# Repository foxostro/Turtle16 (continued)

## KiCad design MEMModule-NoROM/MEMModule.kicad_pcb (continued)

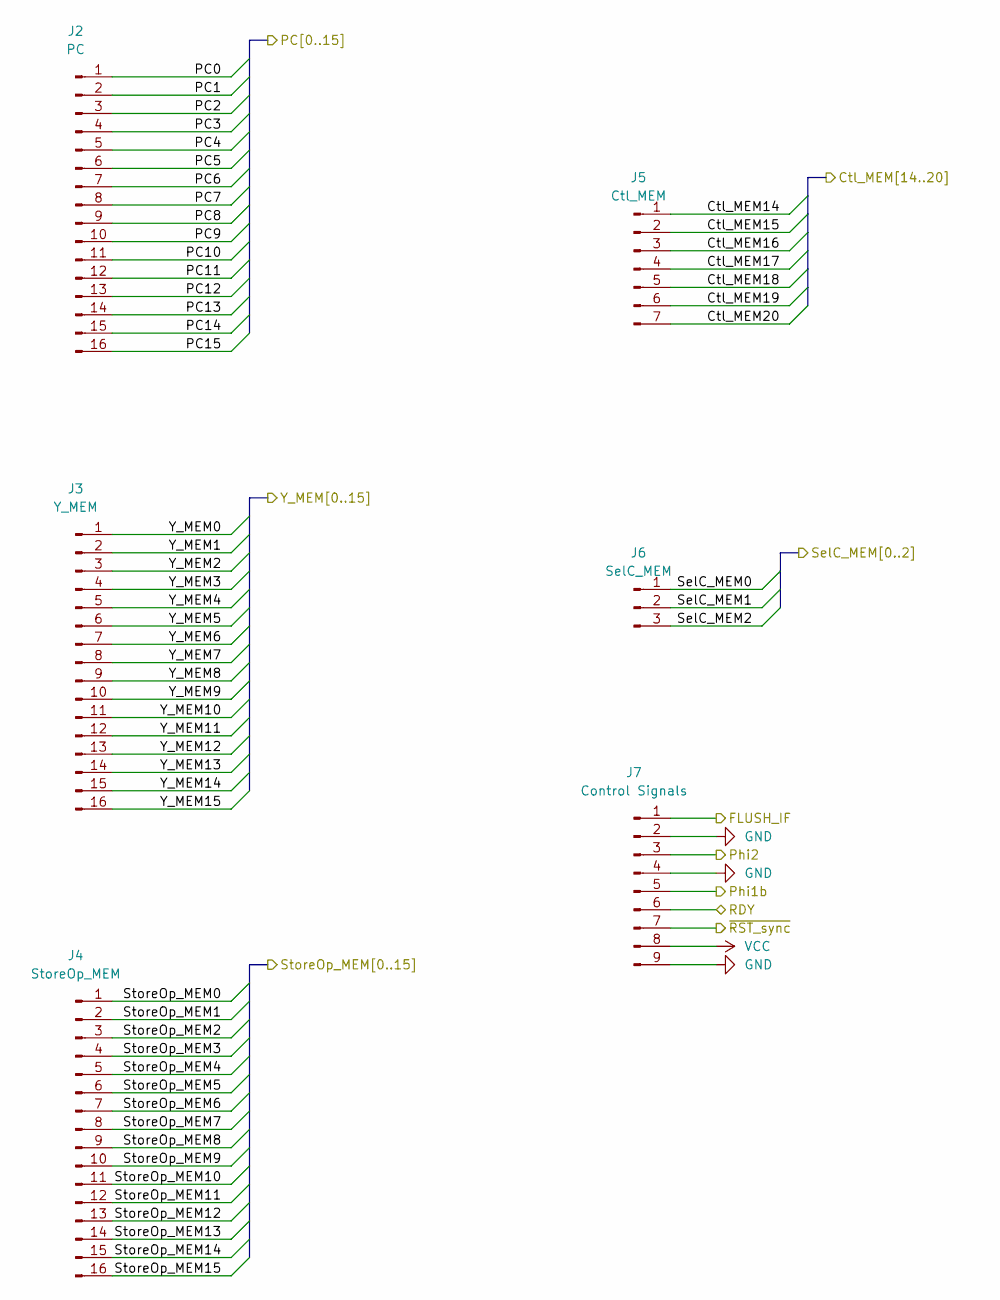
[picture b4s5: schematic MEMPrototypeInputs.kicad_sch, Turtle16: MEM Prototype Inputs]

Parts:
J2: PC; PinHeader_1x16_P2.54mm_Vertical
J3: Y_MEM; PinHeader_1x16_P2.54mm_Vertical
J4: StoreOp_MEM; PinHeader_1x16_P2.54mm_Vertical
J5: Ctl_MEM; PinHeader_1x07_P2.54mm_Vertical
J6: SelC_MEM; PinHeader_1x03_P2.54mm_Vertical
J7: Control Signals; PinHeader_1x09_P2.54mm_Vertical

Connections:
/MEM Prototype Inputs/Ctl_MEM14: J5.1; also elsewhere on the board
/MEM Prototype Inputs/Ctl_MEM15: J5.2; also elsewhere on the board
/MEM Prototype Inputs/Ctl_MEM16: J5.3; also elsewhere on the board
/MEM Prototype Inputs/Ctl_MEM17: J5.4; also elsewhere on the board
/MEM Prototype Inputs/Ctl_MEM18: J5.5; also elsewhere on the board
/MEM Prototype Inputs/Ctl_MEM19: J5.6; also elsewhere on the board
/MEM Prototype Inputs/Ctl_MEM20: J5.7; also elsewhere on the board
/MEM Prototype Inputs/FLUSH_IF: J7.1; also elsewhere on the board
/MEM Prototype Inputs/Phi1b: J7.5; also elsewhere on the board
/MEM Prototype Inputs/Phi2: J7.3; also elsewhere on the board
/MEM Prototype Inputs/RDY: J7.6; also elsewhere on the board
/MEM Prototype Inputs/SelC_MEM0: J6.1; also elsewhere on the board
/MEM Prototype Inputs/SelC_MEM1: J6.2; also elsewhere on the board
/MEM Prototype Inputs/SelC_MEM2: J6.3; also elsewhere on the board
/MEM Prototype Inputs/StoreOp_MEM0: J4.1; also elsewhere on the board
/MEM Prototype Inputs/StoreOp_MEM1: J4.2; also elsewhere on the board
/MEM Prototype Inputs/StoreOp_MEM2: J4.3; also elsewhere on the board
/MEM Prototype Inputs/StoreOp_MEM3: J4.4; also elsewhere on the board
/MEM Prototype Inputs/StoreOp_MEM4: J4.5; also elsewhere on the board
/MEM Prototype Inputs/StoreOp_MEM5: J4.6; also elsewhere on the board
/MEM Prototype Inputs/StoreOp_MEM6: J4.7; also elsewhere on the board
/MEM Prototype Inputs/StoreOp_MEM7: J4.8; also elsewhere on the board
/MEM Prototype Inputs/StoreOp_MEM8: J4.9; also elsewhere on the board
/MEM Prototype Inputs/StoreOp_MEM9: J4.10; also elsewhere on the board
/MEM Prototype Inputs/StoreOp_MEM10: J4.11; also elsewhere on the board
/MEM Prototype Inputs/StoreOp_MEM11: J4.12; also elsewhere on the board
/MEM Prototype Inputs/StoreOp_MEM12: J4.13; also elsewhere on the board
/MEM Prototype Inputs/StoreOp_MEM13: J4.14; also elsewhere on the board
/MEM Prototype Inputs/StoreOp_MEM14: J4.15; also elsewhere on the board
/MEM Prototype Inputs/StoreOp_MEM15: J4.16; also elsewhere on the board
/MEM Prototype Inputs/Y_MEM0: J3.1; also elsewhere on the board
/MEM Prototype Inputs/Y_MEM1: J3.2; also elsewhere on the board
/MEM Prototype Inputs/Y_MEM2: J3.3; also elsewhere on the board
/MEM Prototype Inputs/Y_MEM3: J3.4; also elsewhere on the board
/MEM Prototype Inputs/Y_MEM4: J3.5; also elsewhere on the board
/MEM Prototype Inputs/Y_MEM5: J3.6; also elsewhere on the board
/MEM Prototype Inputs/Y_MEM6: J3.7; also elsewhere on the board
/MEM Prototype Inputs/Y_MEM7: J3.8; also elsewhere on the board
/MEM Prototype Inputs/Y_MEM8: J3.9; also elsewhere on the board
/MEM Prototype Inputs/Y_MEM9: J3.10; also elsewhere on the board
/MEM Prototype Inputs/Y_MEM10: J3.11; also elsewhere on the board
/MEM Prototype Inputs/Y_MEM11: J3.12; also elsewhere on the board
/MEM Prototype Inputs/Y_MEM12: J3.13; also elsewhere on the board
/MEM Prototype Inputs/Y_MEM13: J3.14; also elsewhere on the board
/MEM Prototype Inputs/Y_MEM14: J3.15; also elsewhere on the board
/MEM Prototype Inputs/Y_MEM15: J3.16; also elsewhere on the board
/MEM Prototype Inputs/~RST_sync: J7.7; also elsewhere on the board
/RAM/PC0: J2.1; also elsewhere on the board
/RAM/PC1: J2.2; also elsewhere on the board
/RAM/PC2: J2.3; also elsewhere on the board
/RAM/PC3: J2.4; also elsewhere on the board
/RAM/PC4: J2.5; also elsewhere on the board
/RAM/PC5: J2.6; also elsewhere on the board
/RAM/PC6: J2.7; also elsewhere on the board
/RAM/PC7: J2.8; also elsewhere on the board
/RAM/PC8: J2.9; also elsewhere on the board
/RAM/PC9: J2.10; also elsewhere on the board
/RAM/PC10: J2.11; also elsewhere on the board
/RAM/PC11: J2.12; also elsewhere on the board
/RAM/PC12: J2.13; also elsewhere on the board
/RAM/PC13: J2.14; also elsewhere on the board
/RAM/PC14: J2.15; also elsewhere on the board
/RAM/PC15: J2.16; also elsewhere on the board
GND: J7.2, J7.4, J7.9; also elsewhere on the board
VCC: J7.8; also elsewhere on the board

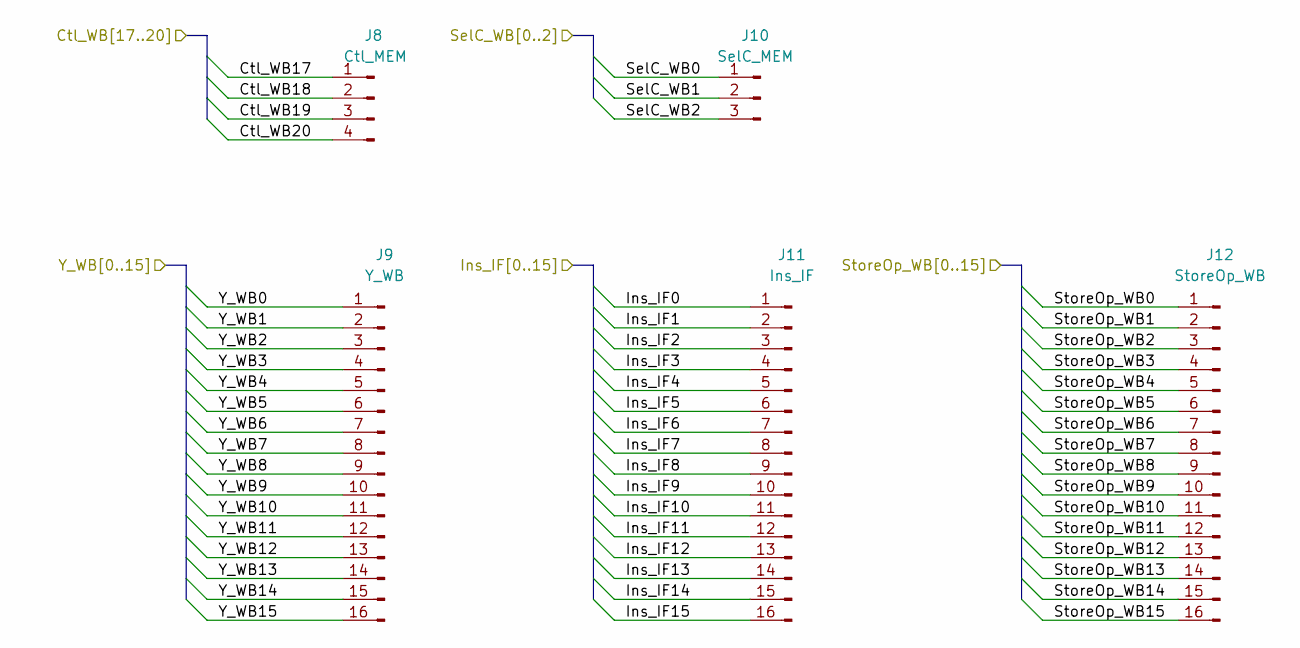
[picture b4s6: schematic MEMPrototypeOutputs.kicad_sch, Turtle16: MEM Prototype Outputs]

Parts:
J8: Ctl_MEM; PinHeader_1x04_P2.54mm_Vertical
J9: Y_WB; PinHeader_1x16_P2.54mm_Vertical
J10: SelC_MEM; PinHeader_1x03_P2.54mm_Vertical
J11: Ins_IF; PinHeader_1x16_P2.54mm_Vertical
J12: StoreOp_WB; PinHeader_1x16_P2.54mm_Vertical

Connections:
/MEM Prototype Outputs/Ctl_WB17: J8.1; also elsewhere on the board
/MEM Prototype Outputs/Ctl_WB18: J8.2; also elsewhere on the board
/MEM Prototype Outputs/Ctl_WB19: J8.3; also elsewhere on the board
/MEM Prototype Outputs/Ctl_WB20: J8.4; also elsewhere on the board
/MEM Prototype Outputs/SelC_WB0: J10.1; also elsewhere on the board
/MEM Prototype Outputs/SelC_WB1: J10.2; also elsewhere on the board
/MEM Prototype Outputs/SelC_WB2: J10.3; also elsewhere on the board
/MEM Prototype Outputs/StoreOp_WB0: J12.1; also elsewhere on the board
/MEM Prototype Outputs/StoreOp_WB1: J12.2; also elsewhere on the board
/MEM Prototype Outputs/StoreOp_WB2: J12.3; also elsewhere on the board
/MEM Prototype Outputs/StoreOp_WB3: J12.4; also elsewhere on the board
/MEM Prototype Outputs/StoreOp_WB4: J12.5; also elsewhere on the board
/MEM Prototype Outputs/StoreOp_WB5: J12.6; also elsewhere on the board
/MEM Prototype Outputs/StoreOp_WB6: J12.7; also elsewhere on the board
/MEM Prototype Outputs/StoreOp_WB7: J12.8; also elsewhere on the board
/MEM Prototype Outputs/StoreOp_WB8: J12.9; also elsewhere on the board
/MEM Prototype Outputs/StoreOp_WB9: J12.10; also elsewhere on the board
/MEM Prototype Outputs/StoreOp_WB10: J12.11; also elsewhere on the board
/MEM Prototype Outputs/StoreOp_WB11: J12.12; also elsewhere on the board
/MEM Prototype Outputs/StoreOp_WB12: J12.13; also elsewhere on the board
/MEM Prototype Outputs/StoreOp_WB13: J12.14; also elsewhere on the board
/MEM Prototype Outputs/StoreOp_WB14: J12.15; also elsewhere on the board
/MEM Prototype Outputs/StoreOp_WB15: J12.16; also elsewhere on the board
/MEM Prototype Outputs/Y_WB0: J9.1; also elsewhere on the board
/MEM Prototype Outputs/Y_WB1: J9.2; also elsewhere on the board
/MEM Prototype Outputs/Y_WB2: J9.3; also elsewhere on the board
/MEM Prototype Outputs/Y_WB3: J9.4; also elsewhere on the board
/MEM Prototype Outputs/Y_WB4: J9.5; also elsewhere on the board
/MEM Prototype Outputs/Y_WB5: J9.6; also elsewhere on the board
/MEM Prototype Outputs/Y_WB6: J9.7; also elsewhere on the board
/MEM Prototype Outputs/Y_WB7: J9.8; also elsewhere on the board
/MEM Prototype Outputs/Y_WB8: J9.9; also elsewhere on the board
/MEM Prototype Outputs/Y_WB9: J9.10; also elsewhere on the board
/MEM Prototype Outputs/Y_WB10: J9.11; also elsewhere on the board
/MEM Prototype Outputs/Y_WB11: J9.12; also elsewhere on the board
/MEM Prototype Outputs/Y_WB12: J9.13; also elsewhere on the board
/MEM Prototype Outputs/Y_WB13: J9.14; also elsewhere on the board
/MEM Prototype Outputs/Y_WB14: J9.15; also elsewhere on the board
/MEM Prototype Outputs/Y_WB15: J9.16; also elsewhere on the board
/RAM/Ins_IF0: J11.1; also elsewhere on the board
/RAM/Ins_IF1: J11.2; also elsewhere on the board
/RAM/Ins_IF2: J11.3; also elsewhere on the board
/RAM/Ins_IF3: J11.4; also elsewhere on the board
/RAM/Ins_IF4: J11.5; also elsewhere on the board
/RAM/Ins_IF5: J11.6; also elsewhere on the board
/RAM/Ins_IF6: J11.7; also elsewhere on the board
/RAM/Ins_IF7: J11.8; also elsewhere on the board
/RAM/Ins_IF8: J11.9; also elsewhere on the board
/RAM/Ins_IF9: J11.10; also elsewhere on the board
/RAM/Ins_IF10: J11.11; also elsewhere on the board
/RAM/Ins_IF11: J11.12; also elsewhere on the board
/RAM/Ins_IF12: J11.13; also elsewhere on the board
/RAM/Ins_IF13: J11.14; also elsewhere on the board
/RAM/Ins_IF14: J11.15; also elsewhere on the board
/RAM/Ins_IF15: J11.16; also elsewhere on the board

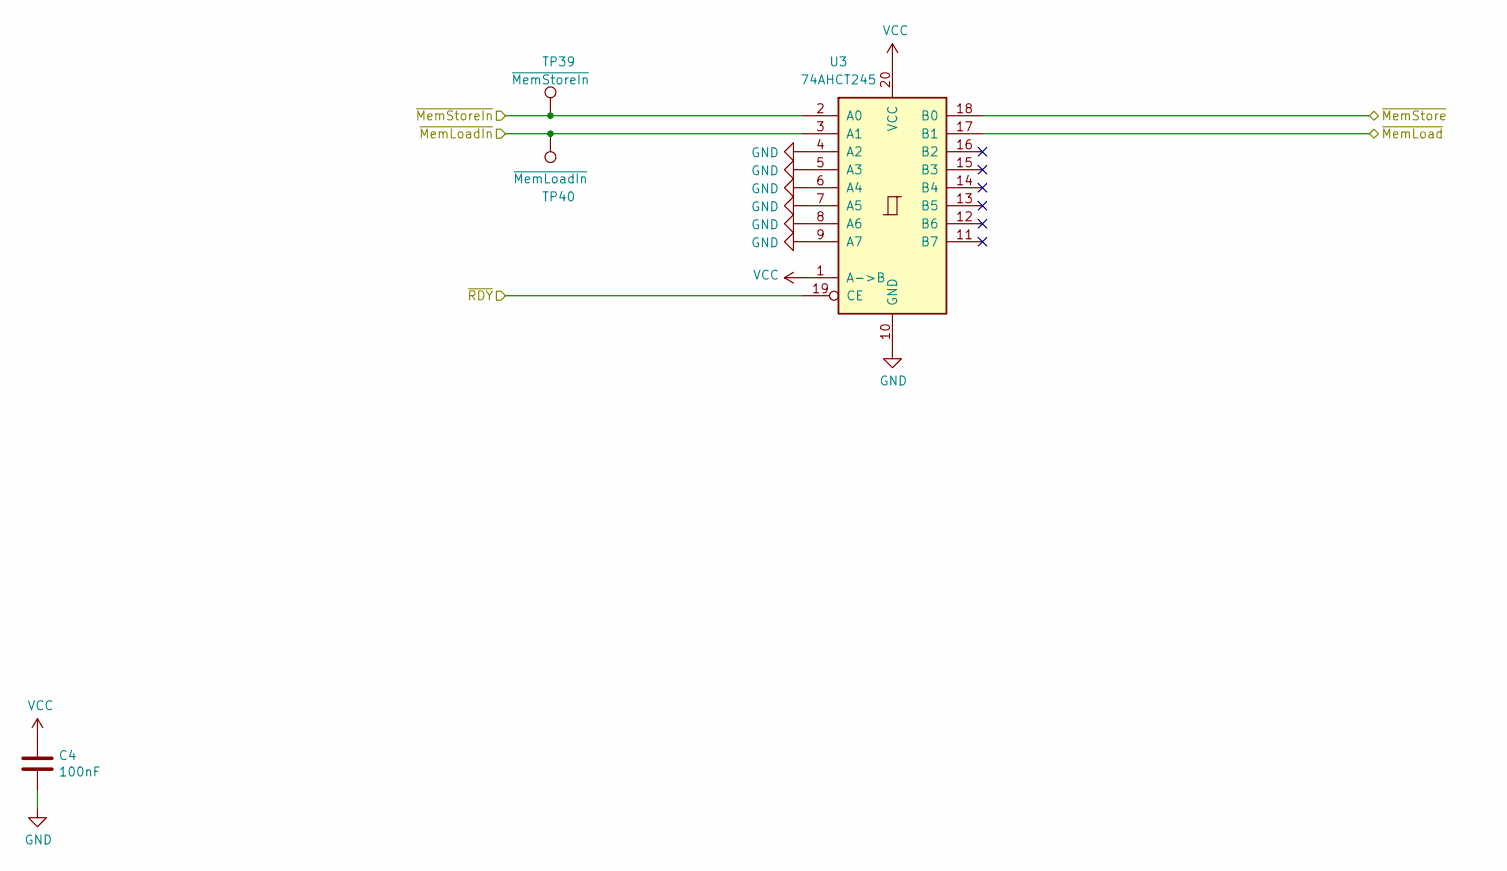
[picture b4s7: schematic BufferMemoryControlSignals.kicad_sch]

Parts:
C4: 100nF; C_0603_1608Metric_Pad1.08x0.95mm_HandSolder
TP39: ~{MemStoreIn}; TestPoint_Pad_D1.0mm
TP40: ~{MemLoadIn}; TestPoint_Pad_D1.0mm
U3: 74AHCT245; TSSOP-20_4.4x6.5mm_P0.65mm

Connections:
/MEM Prototype Inputs/Ctl_MEM14: TP40.1, U3.3 (A1); also elsewhere on the board
/MEM Prototype Inputs/Ctl_MEM15: TP39.1, U3.2 (A0); also elsewhere on the board
/MEM/~RDY: U3.19 (CE); also elsewhere on the board
/System Bus Connector/~MemLoad: U3.17 (B1); also elsewhere on the board
/System Bus Connector/~MemStore: U3.18 (B0); also elsewhere on the board
GND: C4.2, U3.4 (A2), U3.5 (A3), U3.6 (A4), U3.7 (A5), U3.8 (A6), U3.9 (A7), U3.10 (GND); also elsewhere on the board
VCC: C4.1, U3.1 (A->B), U3.20 (VCC); also elsewhere on the board

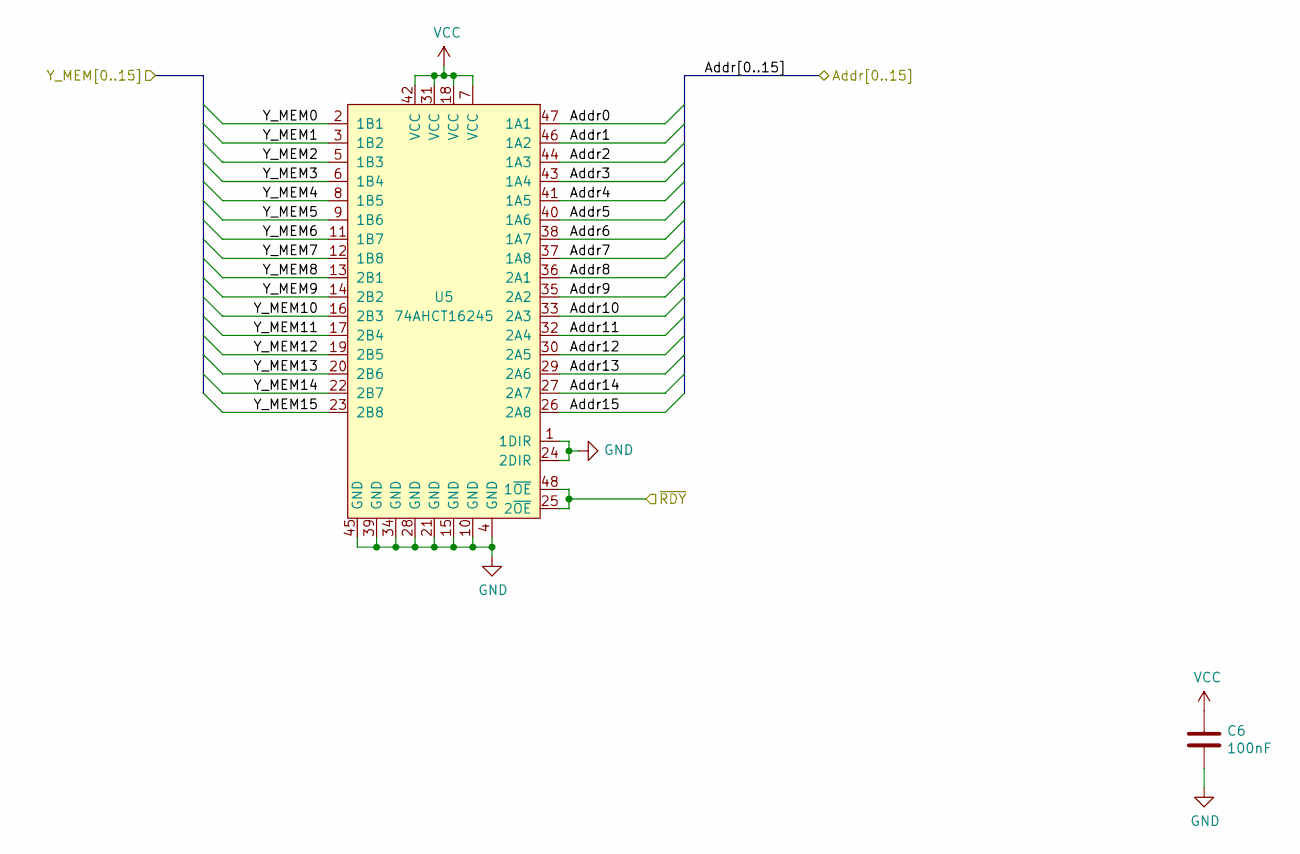
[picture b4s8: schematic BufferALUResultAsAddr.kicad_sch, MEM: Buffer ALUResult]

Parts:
C6: 100nF; C_0603_1608Metric_Pad1.08x0.95mm_HandSolder
U5: 74AHCT16245; TSSOP-48_6.1x12.5mm_P0.5mm

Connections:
/MEM Prototype Inputs/Y_MEM0: U5.2 (1B1); also elsewhere on the board
/MEM Prototype Inputs/Y_MEM1: U5.3 (1B2); also elsewhere on the board
/MEM Prototype Inputs/Y_MEM2: U5.5 (1B3); also elsewhere on the board
/MEM Prototype Inputs/Y_MEM3: U5.6 (1B4); also elsewhere on the board
/MEM Prototype Inputs/Y_MEM4: U5.8 (1B5); also elsewhere on the board
/MEM Prototype Inputs/Y_MEM5: U5.9 (1B6); also elsewhere on the board
/MEM Prototype Inputs/Y_MEM6: U5.11 (1B7); also elsewhere on the board
/MEM Prototype Inputs/Y_MEM7: U5.12 (1B8); also elsewhere on the board
/MEM Prototype Inputs/Y_MEM8: U5.13 (2B1); also elsewhere on the board
/MEM Prototype Inputs/Y_MEM9: U5.14 (2B2); also elsewhere on the board
/MEM Prototype Inputs/Y_MEM10: U5.16 (2B3); also elsewhere on the board
/MEM Prototype Inputs/Y_MEM11: U5.17 (2B4); also elsewhere on the board
/MEM Prototype Inputs/Y_MEM12: U5.19 (2B5); also elsewhere on the board
/MEM Prototype Inputs/Y_MEM13: U5.20 (2B6); also elsewhere on the board
/MEM Prototype Inputs/Y_MEM14: U5.22 (2B7); also elsewhere on the board
/MEM Prototype Inputs/Y_MEM15: U5.23 (2B8); also elsewhere on the board
/MEM/~RDY: U5.25 (2~OE), U5.48 (1~OE); also elsewhere on the board
/RAM/Addr0: U5.47 (1A1); also elsewhere on the board
/RAM/Addr1: U5.46 (1A2); also elsewhere on the board
/RAM/Addr2: U5.44 (1A3); also elsewhere on the board
/RAM/Addr3: U5.43 (1A4); also elsewhere on the board
/RAM/Addr4: U5.41 (1A5); also elsewhere on the board
/RAM/Addr5: U5.40 (1A6); also elsewhere on the board
/RAM/Addr6: U5.38 (1A7); also elsewhere on the board
/RAM/Addr7: U5.37 (1A8); also elsewhere on the board
/RAM/Addr8: U5.36 (2A1); also elsewhere on the board
/RAM/Addr9: U5.35 (2A2); also elsewhere on the board
/RAM/Addr10: U5.33 (2A3); also elsewhere on the board
/RAM/Addr11: U5.32 (2A4); also elsewhere on the board
/RAM/Addr12: U5.30 (2A5); also elsewhere on the board
/RAM/Addr13: U5.29 (2A6); also elsewhere on the board
/RAM/Addr14: U5.27 (2A7); also elsewhere on the board
/RAM/Addr15: U5.26 (2A8); also elsewhere on the board
GND: C6.2, U5.1 (1DIR), U5.4 (GND), U5.10 (GND), U5.15 (GND), U5.21 (GND), U5.24 (2DIR), U5.28 (GND), U5.34 (GND), U5.39 (GND), U5.45 (GND); also elsewhere on the board
VCC: C6.1, U5.7 (VCC), U5.18 (VCC), U5.31 (VCC), U5.42 (VCC); also elsewhere on the board

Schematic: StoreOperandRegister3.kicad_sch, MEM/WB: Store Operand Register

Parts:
C8: 100nF; C_0603_1608Metric_Pad1.08x0.95mm_HandSolder
U7: 74ABT16374; TSSOP-48_8x12.5mm_P0.5mm

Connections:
/MEM Prototype Inputs/Phi1b: U7.25 (2CLK), U7.48 (1CLK); also elsewhere on the board
/MEM Prototype Outputs/StoreOp_WB0: U7.2 (1Q1); also elsewhere on the board
/MEM Prototype Outputs/StoreOp_WB1: U7.3 (1Q2); also elsewhere on the board
/MEM Prototype Outputs/StoreOp_WB2: U7.5 (1Q3); also elsewhere on the board
/MEM Prototype Outputs/StoreOp_WB3: U7.6 (1Q4); also elsewhere on the board
/MEM Prototype Outputs/StoreOp_WB4: U7.8 (1Q5); also elsewhere on the board
/MEM Prototype Outputs/StoreOp_WB5: U7.9 (1Q6); also elsewhere on the board
/MEM Prototype Outputs/StoreOp_WB6: U7.11 (1Q7); also elsewhere on the board
/MEM Prototype Outputs/StoreOp_WB7: U7.12 (1Q8); also elsewhere on the board
/MEM Prototype Outputs/StoreOp_WB8: U7.13 (2Q1); also elsewhere on the board
/MEM Prototype Outputs/StoreOp_WB9: U7.14 (2Q2); also elsewhere on the board
/MEM Prototype Outputs/StoreOp_WB10: U7.16 (2Q3); also elsewhere on the board
/MEM Prototype Outputs/StoreOp_WB11: U7.17 (2Q4); also elsewhere on the board
/MEM Prototype Outputs/StoreOp_WB12: U7.19 (2Q5); also elsewhere on the board
/MEM Prototype Outputs/StoreOp_WB13: U7.20 (2Q6); also elsewhere on the board
/MEM Prototype Outputs/StoreOp_WB14: U7.22 (2Q7); also elsewhere on the board
/MEM Prototype Outputs/StoreOp_WB15: U7.23 (2Q8); also elsewhere on the board
/RAM/IO0: U7.47 (1D1); also elsewhere on the board
/RAM/IO1: U7.46 (1D2); also elsewhere on the board
/RAM/IO2: U7.44 (1D3); also elsewhere on the board
/RAM/IO3: U7.43 (1D4); also elsewhere on the board
/RAM/IO4: U7.41 (1D5); also elsewhere on the board
/RAM/IO5: U7.40 (1D6); also elsewhere on the board
/RAM/IO6: U7.38 (1D7); also elsewhere on the board
/RAM/IO7: U7.37 (1D8); also elsewhere on the board
/RAM/IO8: U7.36 (2D1); also elsewhere on the board
/RAM/IO9: U7.35 (2D2); also elsewhere on the board
/RAM/IO10: U7.33 (2D3); also elsewhere on the board
/RAM/IO11: U7.32 (2D4); also elsewhere on the board
/RAM/IO12: U7.30 (2D5); also elsewhere on the board
/RAM/IO13: U7.29 (2D6); also elsewhere on the board
/RAM/IO14: U7.27 (2D7); also elsewhere on the board
/RAM/IO15: U7.26 (2D8); also elsewhere on the board
GND: C8.2, U7.1 (1~OE), U7.4 (GND), U7.10 (GND), U7.15 (GND), U7.21 (GND), U7.24 (2~OE), U7.28 (GND), U7.34 (GND), U7.39 (GND), U7.45 (GND); also elsewhere on the board
VCC: C8.1, U7.7 (VCC), U7.18 (VCC), U7.31 (VCC), U7.42 (VCC); also elsewhere on the board

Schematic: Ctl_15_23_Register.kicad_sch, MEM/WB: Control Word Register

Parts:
C7: 100nF; C_0603_1608Metric_Pad1.08x0.95mm_HandSolder
U6: 74ABT574; TSSOP-20_4.4x6.5mm_P0.65mm

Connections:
/MEM Prototype Inputs/Ctl_MEM17: U6.9 (D7); also elsewhere on the board
/MEM Prototype Inputs/Ctl_MEM18: U6.8 (D6); also elsewhere on the board
/MEM Prototype Inputs/Ctl_MEM19: U6.7 (D5); also elsewhere on the board
/MEM Prototype Inputs/Ctl_MEM20: U6.6 (D4); also elsewhere on the board
/MEM Prototype Inputs/Phi1b: U6.11 (Cp); also elsewhere on the board
/MEM Prototype Inputs/SelC_MEM0: U6.5 (D3); also elsewhere on the board
/MEM Prototype Inputs/SelC_MEM1: U6.4 (D2); also elsewhere on the board
/MEM Prototype Inputs/SelC_MEM2: U6.3 (D1); also elsewhere on the board
/MEM Prototype Outputs/Ctl_WB17: U6.12 (Q7); also elsewhere on the board
/MEM Prototype Outputs/Ctl_WB18: U6.13 (Q6); also elsewhere on the board
/MEM Prototype Outputs/Ctl_WB19: U6.14 (Q5); also elsewhere on the board
/MEM Prototype Outputs/Ctl_WB20: U6.15 (Q4); also elsewhere on the board
/MEM Prototype Outputs/SelC_WB0: U6.16 (Q3); also elsewhere on the board
/MEM Prototype Outputs/SelC_WB1: U6.17 (Q2); also elsewhere on the board
/MEM Prototype Outputs/SelC_WB2: U6.18 (Q1); also elsewhere on the board
GND: C7.2, U6.1 (OE), U6.10 (GND); also elsewhere on the board
VCC: C7.1, U6.2 (D0), U6.20 (VCC); also elsewhere on the board

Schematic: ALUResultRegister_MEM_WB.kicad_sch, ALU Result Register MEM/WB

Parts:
C9: 100nF; C_0603_1608Metric_Pad1.08x0.95mm_HandSolder
U8: 74ABT16374; TSSOP-48_8x12.5mm_P0.5mm

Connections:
/MEM Prototype Inputs/Phi1b: U8.25 (2CLK), U8.48 (1CLK); also elsewhere on the board
/MEM Prototype Inputs/Y_MEM0: U8.47 (1D1); also elsewhere on the board
/MEM Prototype Inputs/Y_MEM1: U8.46 (1D2); also elsewhere on the board
/MEM Prototype Inputs/Y_MEM2: U8.44 (1D3); also elsewhere on the board
/MEM Prototype Inputs/Y_MEM3: U8.43 (1D4); also elsewhere on the board
/MEM Prototype Inputs/Y_MEM4: U8.41 (1D5); also elsewhere on the board
/MEM Prototype Inputs/Y_MEM5: U8.40 (1D6); also elsewhere on the board
/MEM Prototype Inputs/Y_MEM6: U8.38 (1D7); also elsewhere on the board
/MEM Prototype Inputs/Y_MEM7: U8.37 (1D8); also elsewhere on the board
/MEM Prototype Inputs/Y_MEM8: U8.36 (2D1); also elsewhere on the board
/MEM Prototype Inputs/Y_MEM9: U8.35 (2D2); also elsewhere on the board
/MEM Prototype Inputs/Y_MEM10: U8.33 (2D3); also elsewhere on the board
/MEM Prototype Inputs/Y_MEM11: U8.32 (2D4); also elsewhere on the board
/MEM Prototype Inputs/Y_MEM12: U8.30 (2D5); also elsewhere on the board
/MEM Prototype Inputs/Y_MEM13: U8.29 (2D6); also elsewhere on the board
/MEM Prototype Inputs/Y_MEM14: U8.27 (2D7); also elsewhere on the board
/MEM Prototype Inputs/Y_MEM15: U8.26 (2D8); also elsewhere on the board
/MEM Prototype Outputs/Y_WB0: U8.2 (1Q1); also elsewhere on the board
/MEM Prototype Outputs/Y_WB1: U8.3 (1Q2); also elsewhere on the board
/MEM Prototype Outputs/Y_WB2: U8.5 (1Q3); also elsewhere on the board
/MEM Prototype Outputs/Y_WB3: U8.6 (1Q4); also elsewhere on the board
/MEM Prototype Outputs/Y_WB4: U8.8 (1Q5); also elsewhere on the board
/MEM Prototype Outputs/Y_WB5: U8.9 (1Q6); also elsewhere on the board
/MEM Prototype Outputs/Y_WB6: U8.11 (1Q7); also elsewhere on the board
/MEM Prototype Outputs/Y_WB7: U8.12 (1Q8); also elsewhere on the board
/MEM Prototype Outputs/Y_WB8: U8.13 (2Q1); also elsewhere on the board
/MEM Prototype Outputs/Y_WB9: U8.14 (2Q2); also elsewhere on the board
/MEM Prototype Outputs/Y_WB10: U8.16 (2Q3); also elsewhere on the board
/MEM Prototype Outputs/Y_WB11: U8.17 (2Q4); also elsewhere on the board
/MEM Prototype Outputs/Y_WB12: U8.19 (2Q5); also elsewhere on the board
/MEM Prototype Outputs/Y_WB13: U8.20 (2Q6); also elsewhere on the board
/MEM Prototype Outputs/Y_WB14: U8.22 (2Q7); also elsewhere on the board
/MEM Prototype Outputs/Y_WB15: U8.23 (2Q8); also elsewhere on the board
GND: C9.2, U8.1 (1~OE), U8.4 (GND), U8.10 (GND), U8.15 (GND), U8.21 (GND), U8.24 (2~OE), U8.28 (GND), U8.34 (GND), U8.39 (GND), U8.45 (GND); also elsewhere on the board
VCC: C9.1, U8.7 (VCC), U8.18 (VCC), U8.31 (VCC), U8.42 (VCC); also elsewhere on the board

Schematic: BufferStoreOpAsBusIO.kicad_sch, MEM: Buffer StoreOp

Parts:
C5: 100nF; C_0603_1608Metric_Pad1.08x0.95mm_HandSolder
TP41: ~{Assert}; TestPoint_Pad_D1.0mm
U4: 74AHCT16245; TSSOP-48_6.1x12.5mm_P0.5mm

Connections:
/MEM Prototype Inputs/StoreOp_MEM0: U4.23 (2B8); also elsewhere on the board
/MEM Prototype Inputs/StoreOp_MEM1: U4.22 (2B7); also elsewhere on the board
/MEM Prototype Inputs/StoreOp_MEM2: U4.20 (2B6); also elsewhere on the board
/MEM Prototype Inputs/StoreOp_MEM3: U4.19 (2B5); also elsewhere on the board
/MEM Prototype Inputs/StoreOp_MEM4: U4.17 (2B4); also elsewhere on the board
/MEM Prototype Inputs/StoreOp_MEM5: U4.16 (2B3); also elsewhere on the board
/MEM Prototype Inputs/StoreOp_MEM6: U4.14 (2B2); also elsewhere on the board
/MEM Prototype Inputs/StoreOp_MEM7: U4.13 (2B1); also elsewhere on the board
/MEM Prototype Inputs/StoreOp_MEM8: U4.12 (1B8); also elsewhere on the board
/MEM Prototype Inputs/StoreOp_MEM9: U4.11 (1B7); also elsewhere on the board
/MEM Prototype Inputs/StoreOp_MEM10: U4.9 (1B6); also elsewhere on the board
/MEM Prototype Inputs/StoreOp_MEM11: U4.8 (1B5); also elsewhere on the board
/MEM Prototype Inputs/StoreOp_MEM12: U4.6 (1B4); also elsewhere on the board
/MEM Prototype Inputs/StoreOp_MEM13: U4.5 (1B3); also elsewhere on the board
/MEM Prototype Inputs/StoreOp_MEM14: U4.3 (1B2); also elsewhere on the board
/MEM Prototype Inputs/StoreOp_MEM15: U4.2 (1B1); also elsewhere on the board
/MEM/Buffer StoreOp As Bus I/O/~Assert: TP41.1, U4.25 (2~OE), U4.48 (1~OE); also elsewhere on the board
/RAM/IO0: U4.26 (2A8); also elsewhere on the board
/RAM/IO1: U4.27 (2A7); also elsewhere on the board
/RAM/IO2: U4.29 (2A6); also elsewhere on the board
/RAM/IO3: U4.30 (2A5); also elsewhere on the board
/RAM/IO4: U4.32 (2A4); also elsewhere on the board
/RAM/IO5: U4.33 (2A3); also elsewhere on the board
/RAM/IO6: U4.35 (2A2); also elsewhere on the board
/RAM/IO7: U4.36 (2A1); also elsewhere on the board
/RAM/IO8: U4.37 (1A8); also elsewhere on the board
/RAM/IO9: U4.38 (1A7); also elsewhere on the board
/RAM/IO10: U4.40 (1A6); also elsewhere on the board
/RAM/IO11: U4.41 (1A5); also elsewhere on the board
/RAM/IO12: U4.43 (1A4); also elsewhere on the board
/RAM/IO13: U4.44 (1A3); also elsewhere on the board
/RAM/IO14: U4.46 (1A2); also elsewhere on the board
/RAM/IO15: U4.47 (1A1); also elsewhere on the board
GND: C5.2, U4.1 (1DIR), U4.4 (GND), U4.10 (GND), U4.15 (GND), U4.21 (GND), U4.24 (2DIR), U4.28 (GND), U4.34 (GND), U4.39 (GND), U4.45 (GND); also elsewhere on the board
VCC: C5.1, U4.7 (VCC), U4.18 (VCC), U4.31 (VCC), U4.42 (VCC); also elsewhere on the board

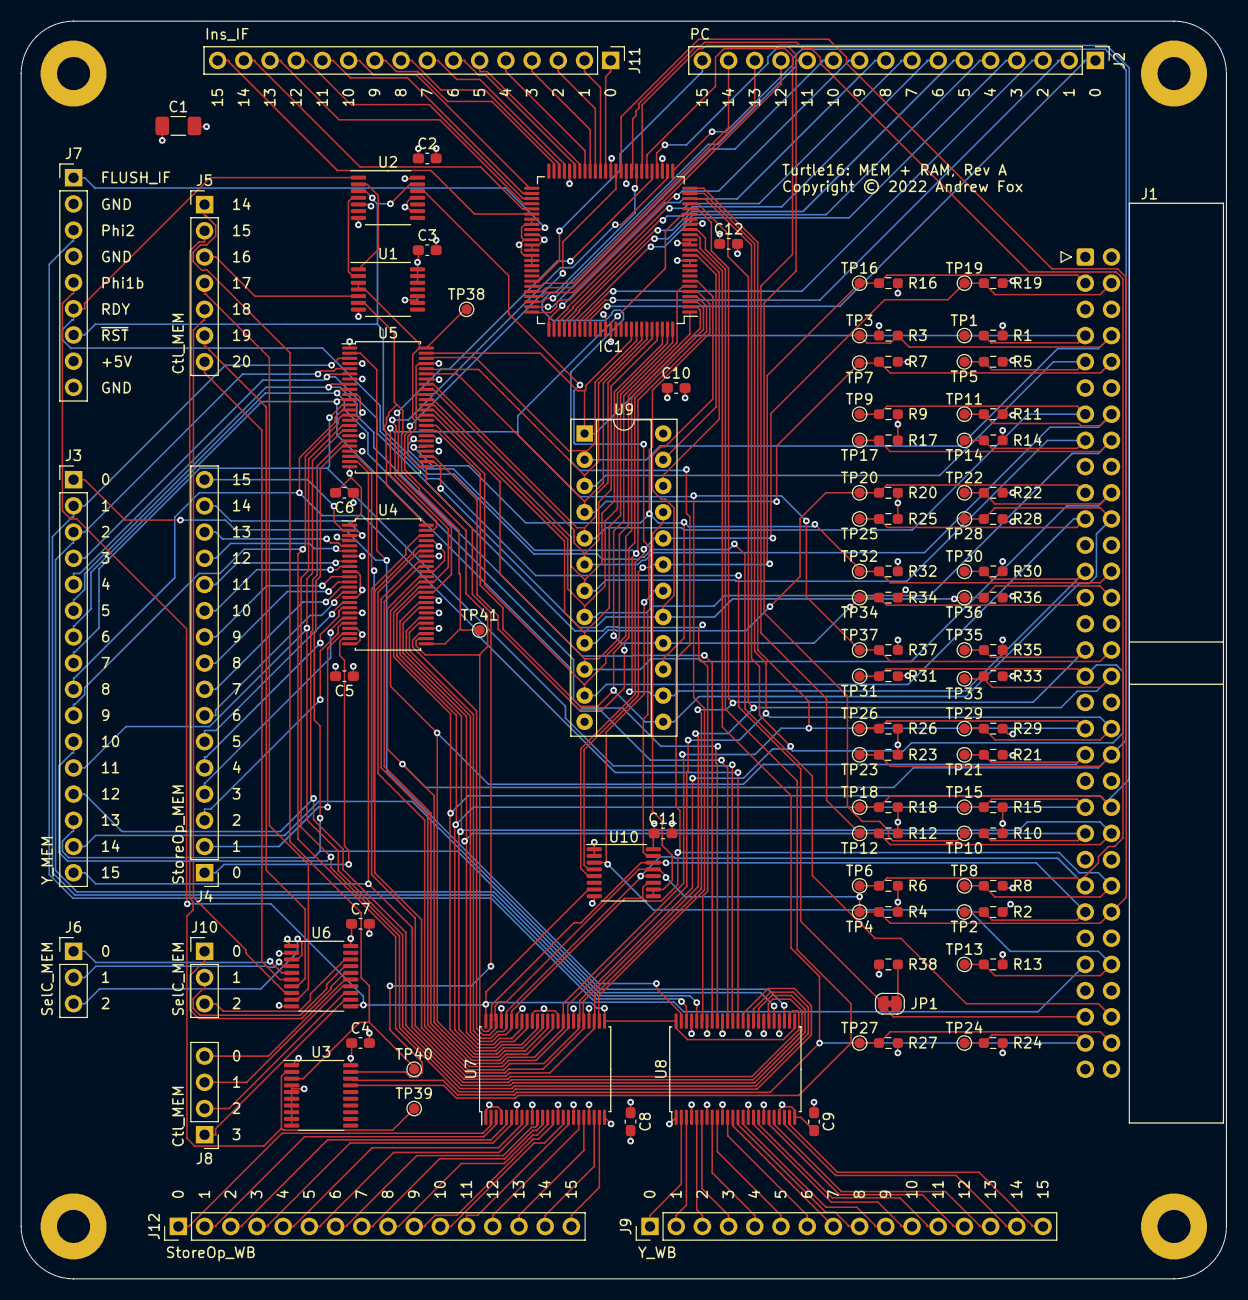
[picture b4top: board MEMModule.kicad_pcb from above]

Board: 4 copper layers, 116.8 x 121.9 mm, 119 parts (0 on the bottom side), 166 nets.
